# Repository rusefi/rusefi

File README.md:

*** test poke do not merge ***

<div align="center">

<b>GPL open-source ECU</b>

</div>

# rusEFI

[shop.rusEFI.com](https://www.shop.rusefi.com/)

# Download

Current binaries are always available on our [build server](http://rusefi.com/build_server/)

# Release Notes

See [the changelog](firmware/CHANGELOG.md)

# What do we have here?
 * [Firmware](/firmware) Source code for open source engine control unit for stm32 chips including [implementation overview](https://github.com/rusefi/rusefi/blob/master/firmware/readme.md)
 * [Hardware](/hardware) KiCAD files for our older PCBs
 * [rusEFI tuner](/java_console) rusEFI's own tuning software
 * [Simulator](/simulator) win32 or posix version of firmware allows to explore without any hardware
 * [Unit Tests](/unit_tests) Unit tests of firmware pieces [coverage report](https://rusefi.com/docs/unit_tests_coverage/)
 * [Misc tools](/java_tools) Misc development utilities
 * [Software Development process](misc/SoftwareDevelopmentProcess.md)

# External Links

 * [Forum](http://rusefi.com/forum)
 * [Documentation](https://wiki.rusefi.com)
 * [Doxygen documentation](http://rusefi.com/docs/html)
 * [General source code Q&A](http://rusefi.com/forum/viewtopic.php?f=5&t=10)
 * [Facebook](https://www.facebook.com/rusEfiECU)
 * [YouTube](https://www.youtube.com/user/rusefi)
 * [Patreon](https://www.patreon.com/rusefi)

# Cloning the repository
`git clone https://github.com/rusefi/rusefi.git`
Important note - we now use submodules:

`git submodule update --init`

# Building the Code

See [gcc_version_check.c](https://github.com/rusefi/rusefi/blob/master/firmware/gcc_version_check.c) for recommended version of GCC.

Check out https://rusefi.com/forum/viewtopic.php?f=5&t=9

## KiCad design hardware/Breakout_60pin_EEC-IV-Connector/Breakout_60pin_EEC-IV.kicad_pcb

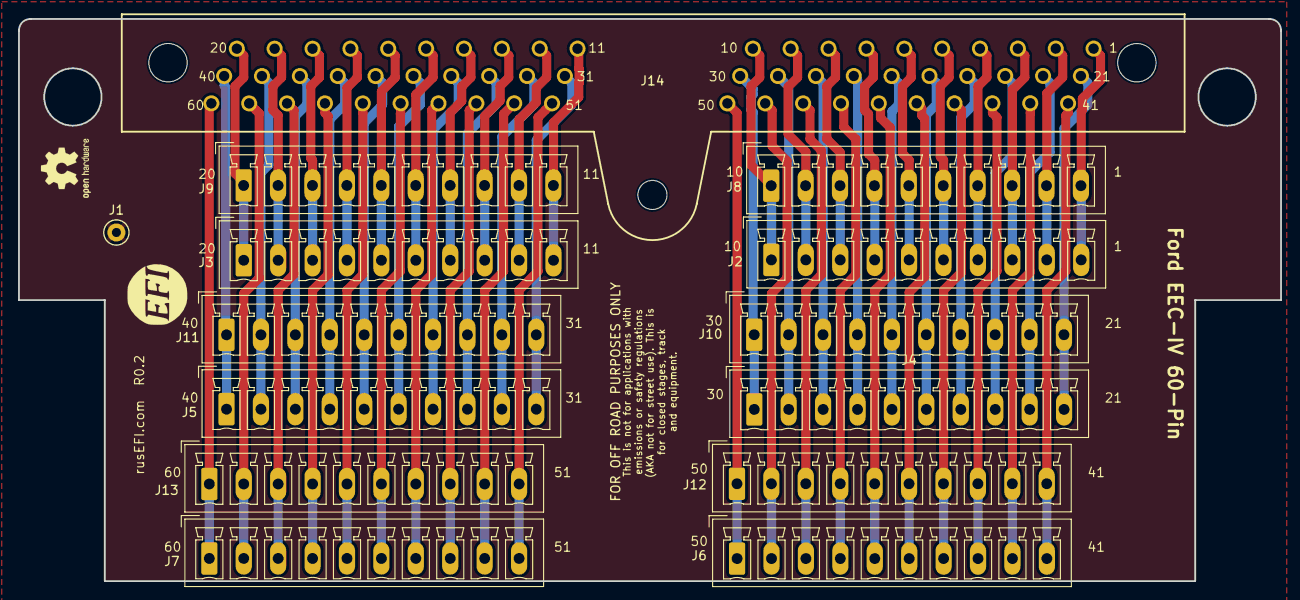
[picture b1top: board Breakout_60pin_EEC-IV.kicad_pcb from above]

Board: 2 copper layers, 139.7 x 62.2 mm, 17 parts (0 on the bottom side), 60 nets.

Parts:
G1: Disclaimer; Off_Road_Disclaimer
G2: LOGO
J1: Conn_01x01; TestPoint_Keystone_5000-5004_Miniature
J2, J3, J4, J5, J6, J7, J8, J9, J10, J11, J12, J13: Conn_01x10; PhoenixContact_MCV_1,5_10-G-3.81_1x10_P3.81mm_Vertical
J14: EEC-IV; eeciv
LOGO1: DNP; OSHW-Logo2_7.3x6mm_SilkScreen

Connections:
/1: J2.10, J8.10, J14.1
/5: J2.6, J8.6, J14.5
/10: J2.1, J8.1, J14.10
/11: J3.10, J9.10, J14.11
/15: J3.6, J9.6, J14.15
/25: J4.6, J10.6, J14.25
/30: J4.1, J10.1, J14.30
/31: J5.10, J11.10, J14.31
/35: J5.6, J11.6, J14.35
/40: J5.1, J11.1, J14.40
/41: J6.10, J12.10, J14.41
/45: J6.6, J12.6, J14.45
/50: J6.1, J12.1, J14.50
/53: J7.8, J13.8, J14.53
/54: J7.7, J13.7, J14.54
/55: J7.6, J13.6, J14.55
/60: J7.1, J13.1, J14.60
/420: J3.1, J9.1, J14.20
/421: J4.10, J10.10, J14.21
unnamed: J4.2, J10.2, J14.29
unnamed: J4.3, J10.3, J14.28
unnamed: J4.4, J10.4, J14.27
unnamed: J4.5, J10.5, J14.26
unnamed: J4.7, J10.7, J14.24
unnamed: J4.8, J10.8, J14.23
unnamed: J4.9, J10.9, J14.22
unnamed: J5.2, J11.2, J14.39
unnamed: J5.3, J11.3, J14.38
unnamed: J5.4, J11.4, J14.37
unnamed: J5.5, J11.5, J14.36
unnamed: J5.7, J11.7, J14.34
unnamed: J5.8, J11.8, J14.33
unnamed: J5.9, J11.9, J14.32
unnamed: J6.2, J12.2, J14.49
unnamed: J6.3, J12.3, J14.48
unnamed: J6.4, J12.4, J14.47
unnamed: J6.5, J12.5, J14.46
unnamed: J6.7, J12.7, J14.44
unnamed: J6.8, J12.8, J14.43
unnamed: J6.9, J12.9, J14.42
unnamed: J7.2, J13.2, J14.59
unnamed: J7.3, J13.3, J14.58
unnamed: J7.4, J13.4, J14.57
unnamed: J7.5, J13.5, J14.56
unnamed: J7.9, J13.9, J14.52
unnamed: J7.10, J13.10, J14.51
unnamed: J2.9, J8.9, J14.2
unnamed: J2.8, J8.8, J14.3
unnamed: J2.7, J8.7, J14.4
unnamed: J2.5, J8.5, J14.6
unnamed: J2.4, J8.4, J14.7
unnamed: J2.3, J8.3, J14.8
unnamed: J2.2, J8.2, J14.9
unnamed: J3.9, J9.9, J14.12
unnamed: J3.8, J9.8, J14.13
unnamed: J3.7, J9.7, J14.14
unnamed: J3.5, J9.5, J14.16
unnamed: J3.4, J9.4, J14.17
unnamed: J3.3, J9.3, J14.18
unnamed: J3.2, J9.2, J14.19

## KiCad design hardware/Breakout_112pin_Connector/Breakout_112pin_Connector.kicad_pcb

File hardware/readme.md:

# Connectors
Some vehicle-specific connector boards are also pretty nice if you want to keep original harness intact

See [Connectors wiki page](http://rusefi.com/wiki/index.php?title=Hardware:OEM_connectors)
todo: move Connectors wiki page content into git

* [35 pin](Breakout_35pin_MX7-C-35PL-C11-connector) Mazda TCU
* [38 pin](Breakout_38pin_NGC-connector) Chrysler NGC connector
* [48 pin](Breakout_48pin_174917-Connector) Mazda Miata NA6
* [52 pin](Breakout_52pin_172319-1-Connector) Mitsubishi Galant VR4
* [55 pin](Breakout_55pin_963063-15-Connector) TE Lada
* [55 pin](breakout_55pin-motronic-Connector) Motronic 1.5.x BMW/GM
* [60 pin](Breakout_60pin_EEC-IV-Connector) Ford EEC-IV
* [64 pin](Breakout_64pin_176122-6-Connector) Mazda Miata NA NB1, Honda Civic
* [68 pin](Breakout_68pin_966595-1_and_963356-1-Connector) Volkswagen Audi VAG
* [72 pin](Breakout_72pin_1123038-2-Connector) Mazda Miata NB2
* [88 pin](Breakout_88pin_VAG-Connector) Volkswagen Audi VAG
* [121 pin](Breakout_121pin_368255-2-Connector) Volkswagen Audi VAG
* [134 pin](Breakout_134pin_7-967288-1-Connector) BWM
* [154 pin](Breakout_154pin_284617-1-Connector) Volkswagen Audi VAG

# Modules
* [stm32 Brain board 48pin](mini48-stm32)
* [stm32 Brain board 100pin](brain_board)
* [stm32 Brain board 176pin](brain_board_176-pin)
* [CAN module](can_board) CAN using SN65HVD230
* [VR module](VR_Board) Variable Reluctance conditioner board VR MAX9926
* [Wideband module](CJ125_board) CJ125 Bosch Wideband board
* [VND5E025AKTR](PowerSSO-24_breakout) double channel high-side driver with analog current sense (used on Dodge Neon 2003 test mule)
* [BTS21400](DDPAK_breakout) ignition coil IGBT driver (used on Dodge Neon 2003 test mule)
* [TLE6240 module](low_side_tle6240) integrated low side switch (fabricated, not tested)
* [TLE6244 module](Breakout_TLE6244) integrated low side switch (never actually fabricated)
* [TLE8810ED module](https://github.com/rusefi/hw_modular/tree/master/TLE8110ED_breakout_board) integrated low side switch
* [MC33816](Common_Rail_MC33816) common rail driver - rusEFI has working GDI*
* [LM1949]([Low-Z_LM1949](https://github.com/rusefi/hw_legacy/tree/master/Low-Z_LM1949)) low impedance injector driver (never actually fabricated)

New modules are being added to https://github.com/rusefi/hw_modular

Some stuff we have given up on completely is located at https://github.com/rusefi/hw_legacy

Above mentioned modules are known to work unless stated otherwise

### More rusEFI hardware

See https://wiki.rusefi.com/Hardware

# Frankenso
Frankenso has moved to https://github.com/rusefi/rusefi-hardware/tree/main/classic-designs

# More info

 [Interactive Html Boms](https://rusefi.com/docs/ibom/)

See [Hardware status forum thread](http://rusefi.com/forum/viewtopic.php?f=4&t=260)
todo: move hardware status content into git

# Important note
rusEFI is currently transitioning from KiCAD 4 to KiCAD 5.

# Important note

Depends on libraries from https://github.com/rusefi/kicad-libraries

If you download complete repo do not forget to download libraries. If you git clone be sure to also

`git submodule update --init`

`git submodule update --init`

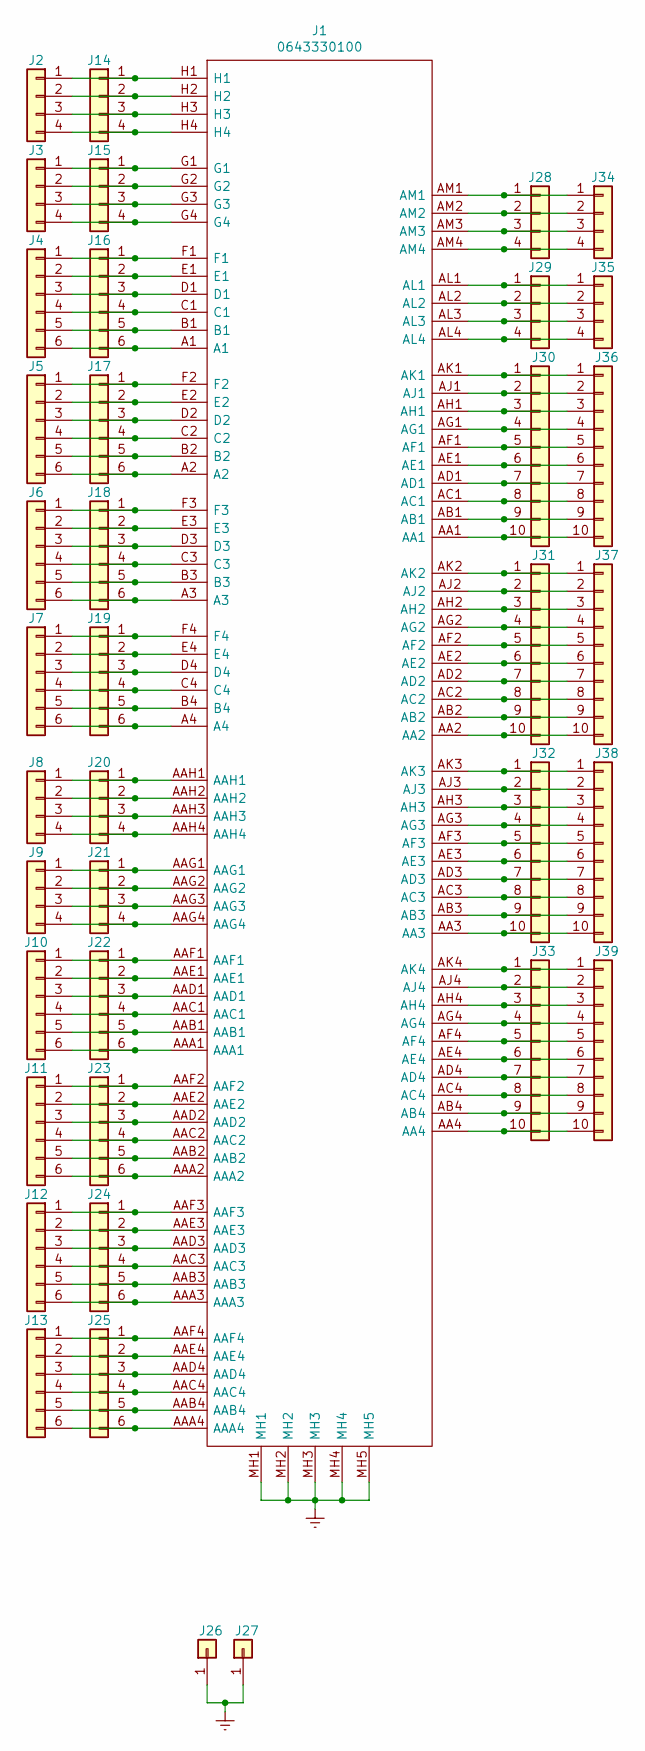
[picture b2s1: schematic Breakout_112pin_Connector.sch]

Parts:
J1: 0643330100; 64333-0100_1; Mouser Part Number N/A
J2, J3, J8, J9, J14, J15, J20, J21, J28, J29, J34, J35: Conn_01x04; Pin_Header_Straight_1x04_Pitch2.54mm
J4, J5, J6, J7, J10, J11, J12, J13, J16, J17, J18, J19, J22, J23, J24, J25: Conn_01x06; Pin_Header_Straight_1x06_Pitch2.54mm
J26, J27: Conn_01x01; Pin_Header_Straight_1x01_Pitch2.54mm
J30, J31, J32, J33, J36, J37, J38, J39: Conn_01x10; Pin_Header_Straight_1x10_Pitch2.54mm

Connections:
Earth: J1.MH1, J1.MH2, J1.MH3, J1.MH4, J1.MH5, J26.1, J27.1
unnamed: J1.A1, J4.6, J16.6
unnamed: J1.A2, J5.6, J17.6
unnamed: J1.A3, J6.6, J18.6
unnamed: J1.A4, J7.6, J19.6
unnamed: J1.AA1, J30.10, J36.10
unnamed: J1.AA2, J31.10, J37.10
unnamed: J1.AA3, J32.10, J38.10
unnamed: J1.AA4, J33.10, J39.10
unnamed: J1.AAA1, J10.6, J22.6
unnamed: J1.AAA2, J11.6, J23.6
unnamed: J1.AAA3, J12.6, J24.6
unnamed: J1.AAA4, J13.6, J25.6
unnamed: J1.AAB1, J10.5, J22.5
unnamed: J1.AAB2, J11.5, J23.5
unnamed: J1.AAB3, J12.5, J24.5
unnamed: J1.AAB4, J13.5, J25.5
unnamed: J1.AAC1, J10.4, J22.4
unnamed: J1.AAC2, J11.4, J23.4
unnamed: J1.AAC3, J12.4, J24.4
unnamed: J1.AAC4, J13.4, J25.4
unnamed: J1.AAD1, J10.3, J22.3
unnamed: J1.AAD2, J11.3, J23.3
unnamed: J1.AAD3, J12.3, J24.3
unnamed: J1.AAD4, J13.3, J25.3
unnamed: J1.AAE1, J10.2, J22.2
unnamed: J1.AAE2, J11.2, J23.2
unnamed: J1.AAE3, J12.2, J24.2
unnamed: J1.AAE4, J13.2, J25.2
unnamed: J1.AAF1, J10.1, J22.1
unnamed: J1.AAF2, J11.1, J23.1
unnamed: J1.AAF3, J12.1, J24.1
unnamed: J1.AAF4, J13.1, J25.1
unnamed: J1.AAG1, J9.1, J21.1
unnamed: J1.AAG2, J9.2, J21.2
unnamed: J1.AAG3, J9.3, J21.3
unnamed: J1.AAG4, J9.4, J21.4
unnamed: J1.AAH1, J8.1, J20.1
unnamed: J1.AAH2, J8.2, J20.2
unnamed: J1.AAH3, J8.3, J20.3
unnamed: J1.AAH4, J8.4, J20.4
unnamed: J1.AB1, J30.9, J36.9
unnamed: J1.AB2, J31.9, J37.9
unnamed: J1.AB3, J32.9, J38.9
unnamed: J1.AB4, J33.9, J39.9
unnamed: J1.AC1, J30.8, J36.8
unnamed: J1.AC2, J31.8, J37.8
unnamed: J1.AC3, J32.8, J38.8
unnamed: J1.AC4, J33.8, J39.8
unnamed: J1.AD1, J30.7, J36.7
unnamed: J1.AD2, J31.7, J37.7
unnamed: J1.AD3, J32.7, J38.7
unnamed: J1.AD4, J33.7, J39.7
unnamed: J1.AE1, J30.6, J36.6
unnamed: J1.AE2, J31.6, J37.6
unnamed: J1.AE3, J32.6, J38.6
unnamed: J1.AE4, J33.6, J39.6
unnamed: J1.AF1, J30.5, J36.5
unnamed: J1.AF2, J31.5, J37.5
unnamed: J1.AF3, J32.5, J38.5
unnamed: J1.AF4, J33.5, J39.5
unnamed: J1.AG1, J30.4, J36.4
unnamed: J1.AG2, J31.4, J37.4
unnamed: J1.AG3, J32.4, J38.4
unnamed: J1.AG4, J33.4, J39.4
unnamed: J1.AH1, J30.3, J36.3
unnamed: J1.AH2, J31.3, J37.3
unnamed: J1.AH3, J32.3, J38.3
unnamed: J1.AH4, J33.3, J39.3
unnamed: J1.AJ1, J30.2, J36.2
unnamed: J1.AJ2, J31.2, J37.2
unnamed: J1.AJ3, J32.2, J38.2
unnamed: J1.AJ4, J33.2, J39.2
unnamed: J1.AK1, J30.1, J36.1
unnamed: J1.AK2, J31.1, J37.1
unnamed: J1.AK3, J32.1, J38.1
unnamed: J1.AK4, J33.1, J39.1
unnamed: J1.AL1, J29.1, J35.1
unnamed: J1.AL2, J29.2, J35.2
unnamed: J1.AL3, J29.3, J35.3
unnamed: J1.AL4, J29.4, J35.4
unnamed: J1.AM1, J28.1, J34.1
unnamed: J1.AM2, J28.2, J34.2
unnamed: J1.AM3, J28.3, J34.3
unnamed: J1.AM4, J28.4, J34.4
unnamed: J1.B1, J4.5, J16.5
unnamed: J1.B2, J5.5, J17.5
unnamed: J1.B3, J6.5, J18.5
unnamed: J1.B4, J7.5, J19.5
unnamed: J1.C1, J4.4, J16.4
unnamed: J1.C2, J5.4, J17.4
unnamed: J1.C3, J6.4, J18.4
unnamed: J1.C4, J7.4, J19.4
unnamed: J1.D1, J4.3, J16.3
unnamed: J1.D2, J5.3, J17.3
unnamed: J1.D3, J6.3, J18.3
unnamed: J1.D4, J7.3, J19.3
unnamed: J1.E1, J4.2, J16.2
unnamed: J1.E2, J5.2, J17.2
unnamed: J1.E3, J6.2, J18.2
unnamed: J1.E4, J7.2, J19.2
unnamed: J1.F1, J4.1, J16.1
unnamed: J1.F2, J5.1, J17.1
unnamed: J1.F3, J6.1, J18.1
unnamed: J1.F4, J7.1, J19.1
unnamed: J1.G1, J3.1, J15.1
unnamed: J1.G2, J3.2, J15.2
unnamed: J1.G3, J3.3, J15.3
unnamed: J1.G4, J3.4, J15.4
unnamed: J1.H1, J2.1, J14.1
unnamed: J1.H2, J2.2, J14.2
unnamed: J1.H3, J2.3, J14.3
unnamed: J1.H4, J2.4, J14.4

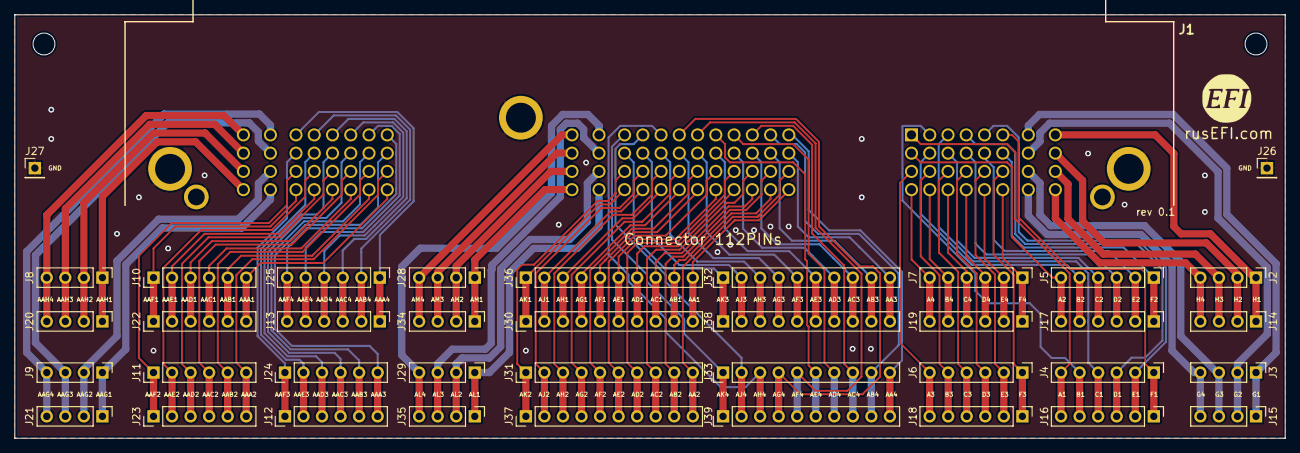
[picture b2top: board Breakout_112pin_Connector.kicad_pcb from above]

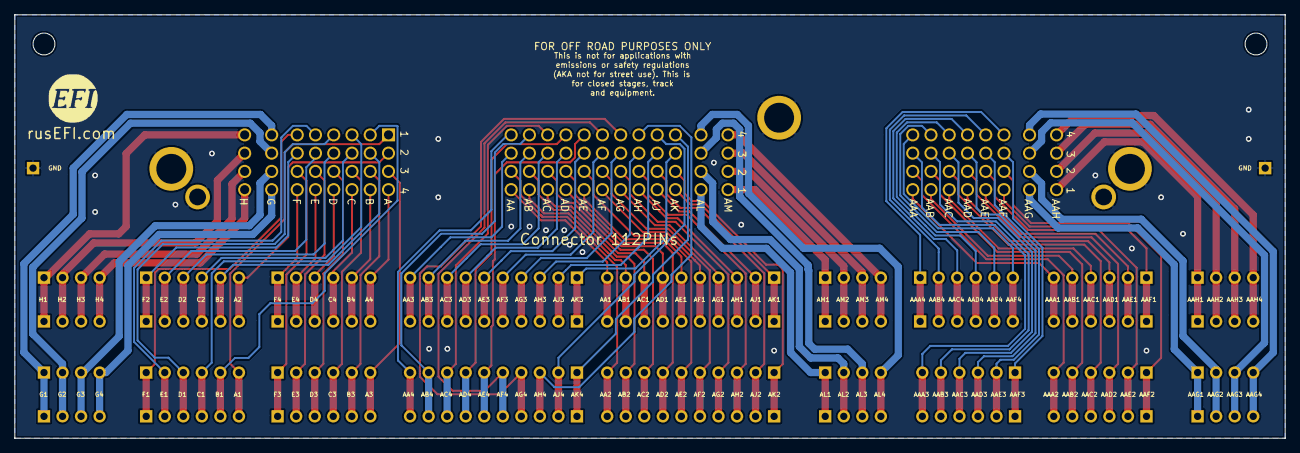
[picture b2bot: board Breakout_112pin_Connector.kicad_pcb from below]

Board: 2 copper layers, 174.0 x 58.0 mm, 42 parts (2 on the bottom side), 113 nets.

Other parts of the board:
G?: LOGO
G?#2: LOGO
G?#3: Disclaimer; Off_Road_Disclaimer

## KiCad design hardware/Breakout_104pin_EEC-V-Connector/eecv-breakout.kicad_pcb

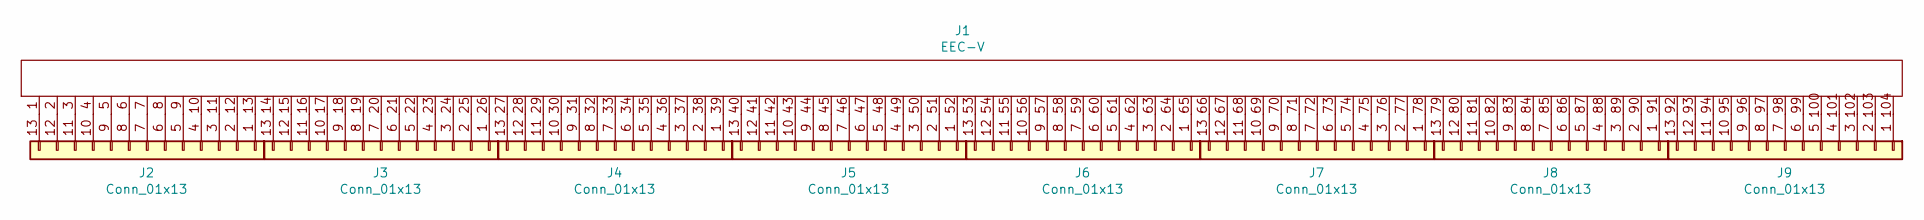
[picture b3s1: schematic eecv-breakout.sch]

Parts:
J1: EEC-V; eecv
J2, J3, J4, J5, J6, J7, J8, J9: Conn_01x13; PhoenixContact_MCV_1,5_13-G-3.81_1x13_P3.81mm_Vertical

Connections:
unnamed: J1.1, J2.13
unnamed: J1.2, J2.12
unnamed: J1.3, J2.11
unnamed: J1.4, J2.10
unnamed: J1.5, J2.9
unnamed: J1.6, J2.8
unnamed: J1.7, J2.7
unnamed: J1.8, J2.6
unnamed: J1.9, J2.5
unnamed: J1.10, J2.4
unnamed: J1.11, J2.3
unnamed: J1.12, J2.2
unnamed: J1.13, J2.1
unnamed: J1.14, J3.13
unnamed: J1.15, J3.12
unnamed: J1.16, J3.11
unnamed: J1.17, J3.10
unnamed: J1.18, J3.9
unnamed: J1.19, J3.8
unnamed: J1.20, J3.7
unnamed: J1.21, J3.6
unnamed: J1.22, J3.5
unnamed: J1.23, J3.4
unnamed: J1.24, J3.3
unnamed: J1.25, J3.2
unnamed: J1.26, J3.1
unnamed: J1.27, J4.13
unnamed: J1.28, J4.12
unnamed: J1.29, J4.11
unnamed: J1.30, J4.10
unnamed: J1.31, J4.9
unnamed: J1.32, J4.8
unnamed: J1.33, J4.7
unnamed: J1.34, J4.6
unnamed: J1.35, J4.5
unnamed: J1.36, J4.4
unnamed: J1.37, J4.3
unnamed: J1.38, J4.2
unnamed: J1.39, J4.1
unnamed: J1.40, J5.13
unnamed: J1.41, J5.12
unnamed: J1.42, J5.11
unnamed: J1.43, J5.10
unnamed: J1.44, J5.9
unnamed: J1.45, J5.8
unnamed: J1.46, J5.7
unnamed: J1.47, J5.6
unnamed: J1.48, J5.5
unnamed: J1.49, J5.4
unnamed: J1.50, J5.3
unnamed: J1.51, J5.2
unnamed: J1.52, J5.1
unnamed: J1.53, J6.13
unnamed: J1.54, J6.12
unnamed: J1.55, J6.11
unnamed: J1.56, J6.10
unnamed: J1.57, J6.9
unnamed: J1.58, J6.8
unnamed: J1.59, J6.7
unnamed: J1.60, J6.6
unnamed: J1.61, J6.5
unnamed: J1.62, J6.4
unnamed: J1.63, J6.3
unnamed: J1.64, J6.2
unnamed: J1.65, J6.1
unnamed: J1.66, J7.13
unnamed: J1.67, J7.12
unnamed: J1.68, J7.11
unnamed: J1.69, J7.10
unnamed: J1.70, J7.9
unnamed: J1.71, J7.8
unnamed: J1.72, J7.7
unnamed: J1.73, J7.6
unnamed: J1.74, J7.5
unnamed: J1.75, J7.4
unnamed: J1.76, J7.3
unnamed: J1.77, J7.2
unnamed: J1.78, J7.1
unnamed: J1.79, J8.13
unnamed: J1.80, J8.12
unnamed: J1.81, J8.11
unnamed: J1.82, J8.10
unnamed: J1.83, J8.9
unnamed: J1.84, J8.8
unnamed: J1.85, J8.7
unnamed: J1.86, J8.6
unnamed: J1.87, J8.5
unnamed: J1.88, J8.4
unnamed: J1.89, J8.3
unnamed: J1.90, J8.2
unnamed: J1.91, J8.1
unnamed: J1.92, J9.13
unnamed: J1.93, J9.12
unnamed: J1.94, J9.11
unnamed: J1.95, J9.10
unnamed: J1.96, J9.9
unnamed: J1.97, J9.8
unnamed: J1.98, J9.7
unnamed: J1.99, J9.6
unnamed: J1.100, J9.5
unnamed: J1.101, J9.4
unnamed: J1.102, J9.3
unnamed: J1.103, J9.2
unnamed: J1.104, J9.1

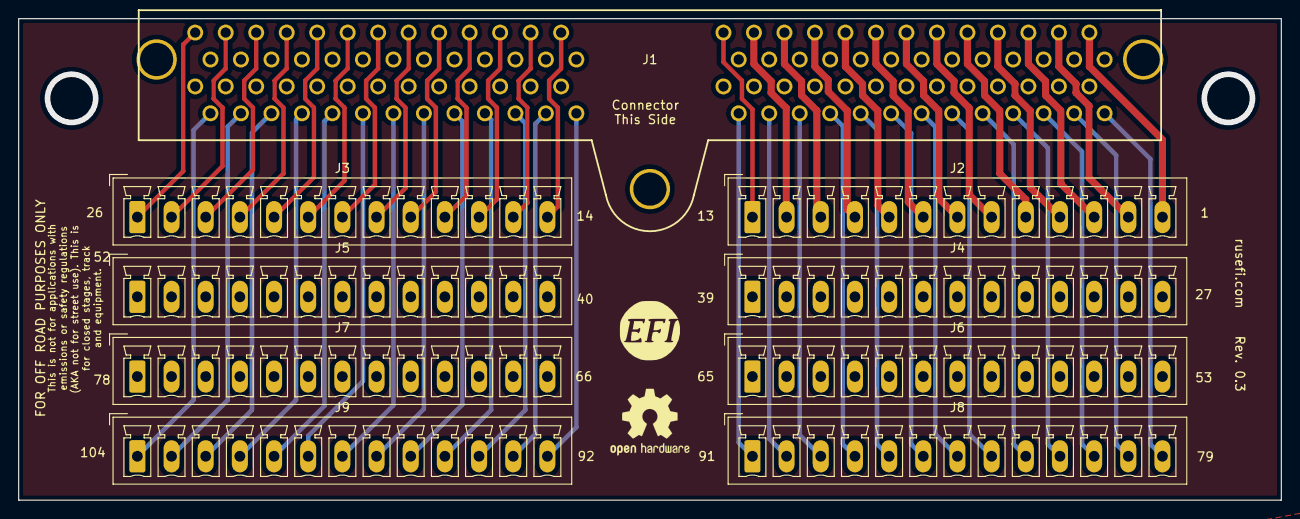
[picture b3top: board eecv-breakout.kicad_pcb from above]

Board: 4 copper layers, 140.8 x 53.7 mm, 11 parts (0 on the bottom side), 104 nets.

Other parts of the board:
G?: LOGO
G?#2: Disclaimer; Off_Road_Disclaimer

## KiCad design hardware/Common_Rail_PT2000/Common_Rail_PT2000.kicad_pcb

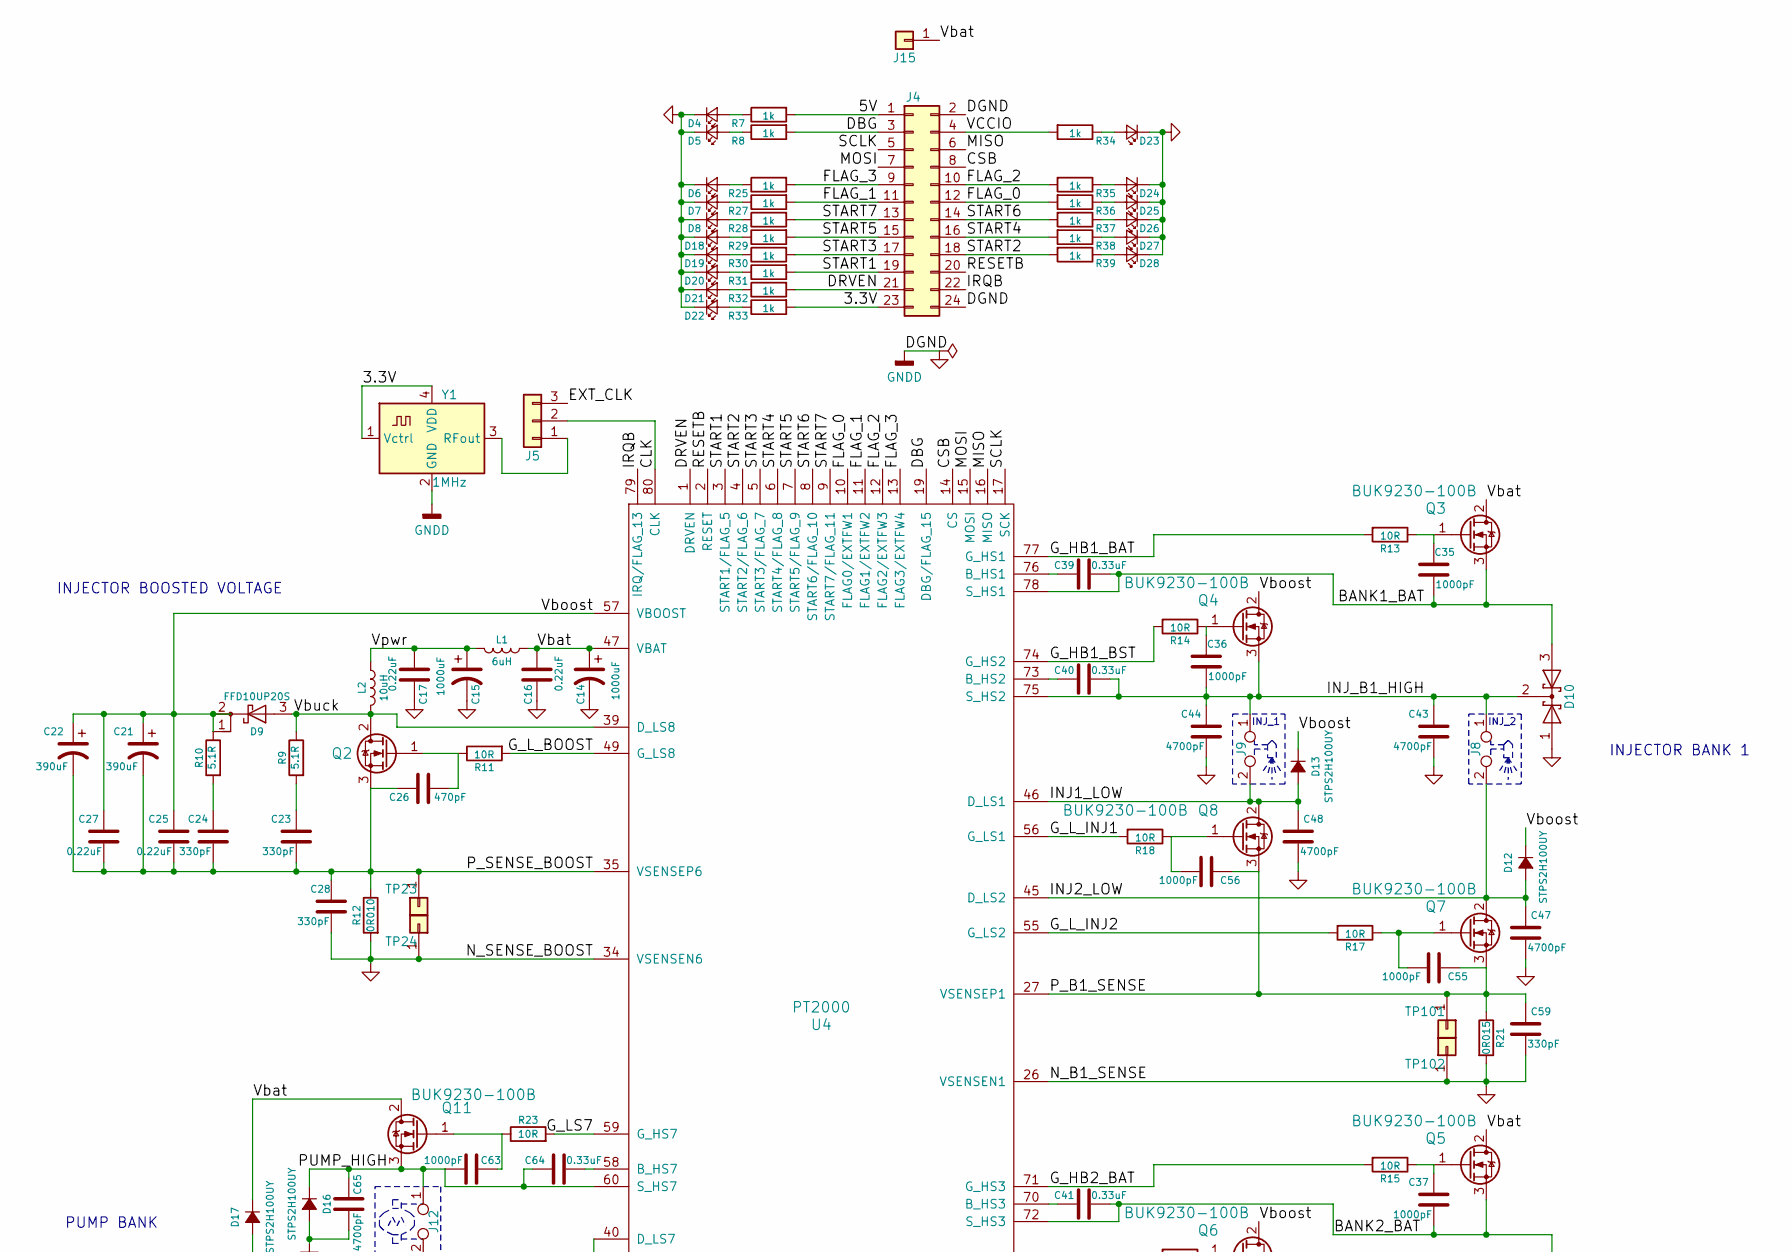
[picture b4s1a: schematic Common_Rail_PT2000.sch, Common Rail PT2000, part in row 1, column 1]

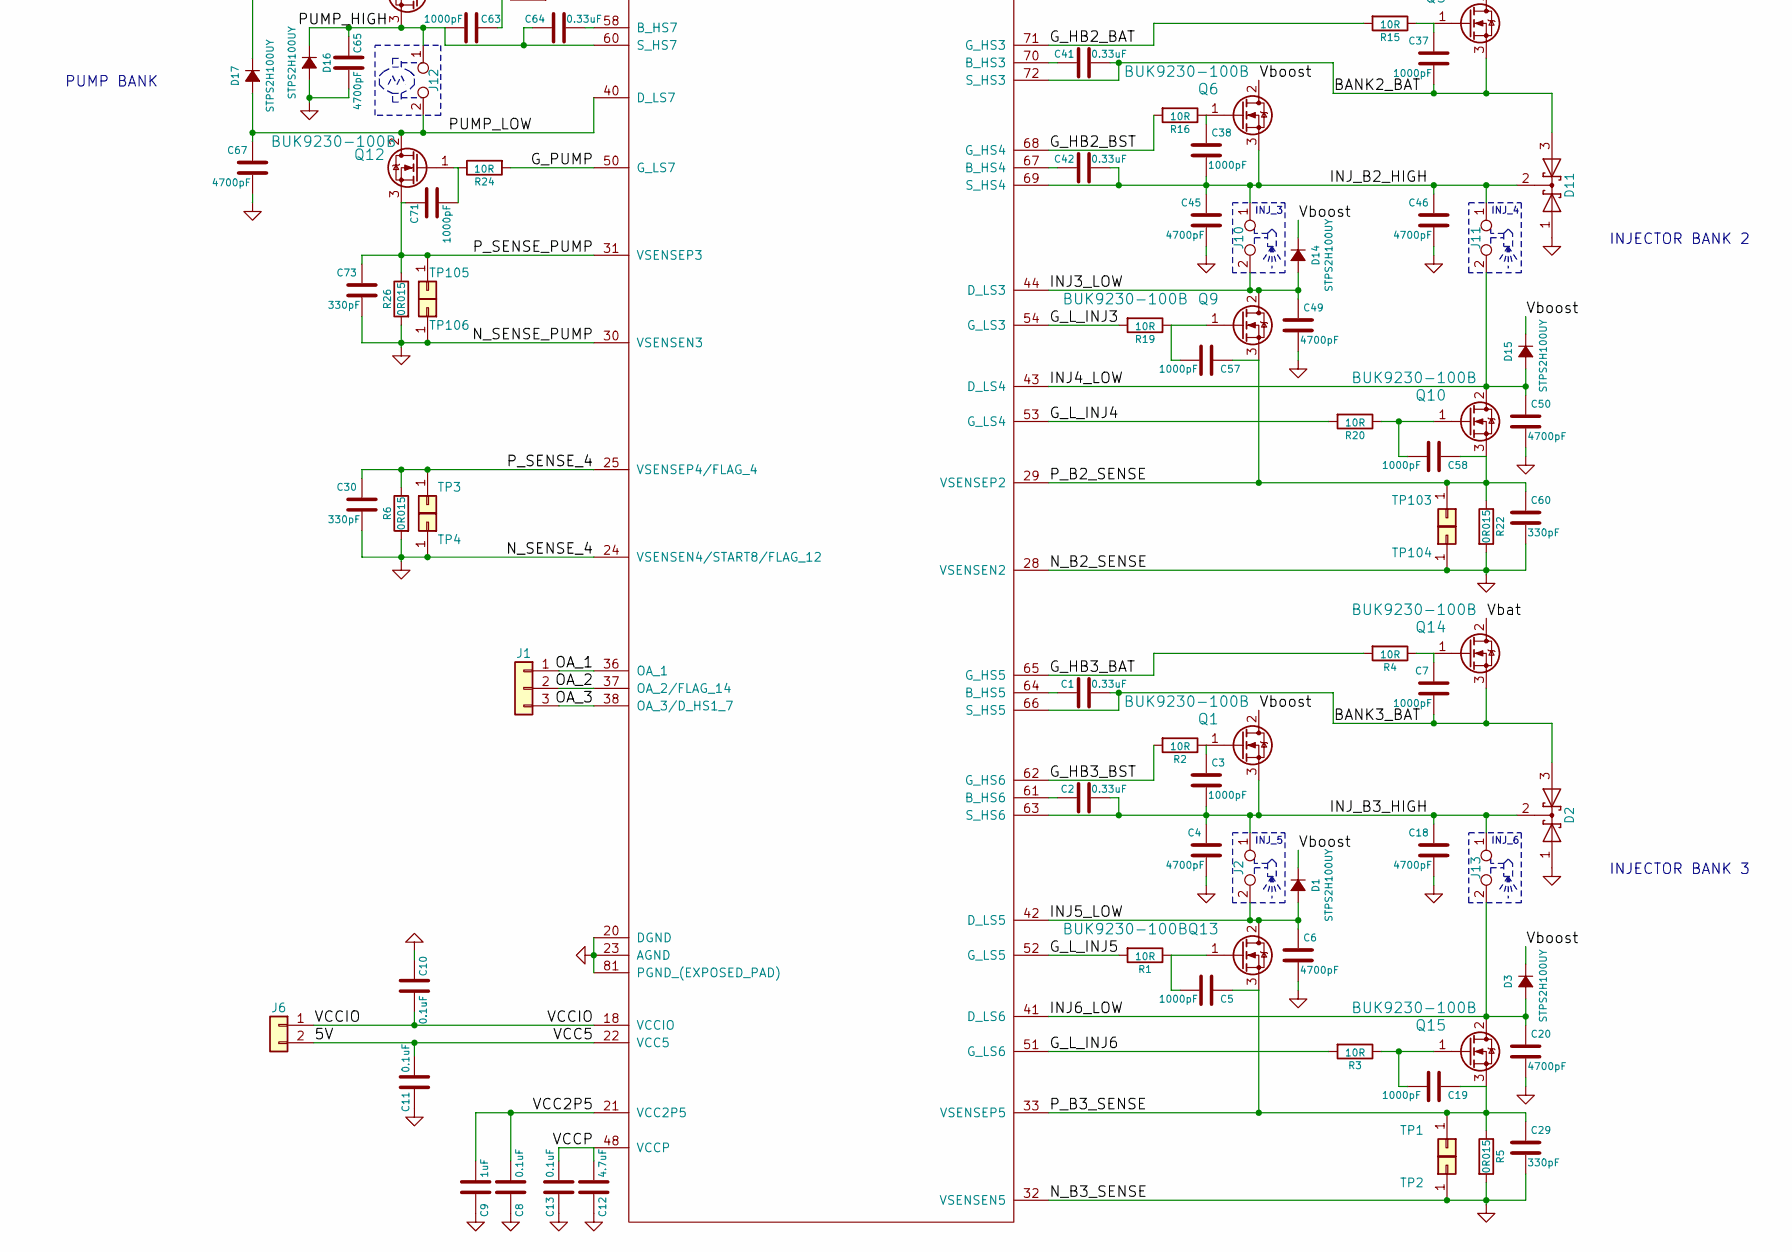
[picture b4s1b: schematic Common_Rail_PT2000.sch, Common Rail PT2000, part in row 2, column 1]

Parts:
C1, C2, C39, C40, C41, C42, C64: 0.33uF; C_0805
C3, C5, C7, C19, C35, C36, C37, C38, C55, C56, C57, C58, C63, C71: 1000pF; C_0805
C4, C6, C18, C20, C43, C44, C45, C46, C47, C48, C49, C50, C65, C67: 4700pF; C_0805
C8, C10, C11, C13: 0.1uF; C_0805
C9: 1uF; C_0805
C12: 4.7uF; C_0805
C14, C15: 1000uF; CP_Radial_D22.0mm_P10.00mm_SnapIn
C16, C17, C25, C27: 0.22uF; C_0805
C21, C22: 390uF; CP_Radial_D16.0mm_P7.50mm
C23, C24, C28, C29, C30, C59, C60, C73: 330pF; C_0805
C26: 470pF; C_0805
D1, D3, D12, D13, D14, D15, D16, D17: STPS2H100UY; D_SMB
D2, D10, D11: SBR10200CTL; TO-252-2Lead
D4, D5, D6, D7, D8, D18, D19, D20, D21, D22, D23, D24, D25, D26, D27, D28: LED_Small; LED_0805
D9: FFD10UP20S; TO-252-2Lead
J1, J5: CONN_01X03; Pin_Header_Straight_1x03_Pitch2.54mm
J2, J8, J9, J10, J11, J12, J13: INJ_Term; TerminalBlock_bornier-2_P5.08mm
J4: CONN_02X08; Pin_Header_Straight_2x12_Pitch2.54mm
J6: CONN_01X03; Pin_Header_Straight_1x02_Pitch1.27mm
J15: Conn_01x01; Pin_Header_Straight_1x01_Pitch2.54mm
L1: 6uH; 744710610-Inductor
L2: 10uH; IHLP6767GZER100M01
Q1, Q2, Q3, Q4, Q5, Q6, Q7, Q8, Q9, Q10, Q11, Q12, Q13, Q14, Q15: BUK9230-100B; TO-252-2Lead
R1, R2, R3, R4, R11, R13, R14, R15, R16, R17, R18, R19, R20, R23, R24: 10R; R_0805
R5, R6, R21, R22, R26: 0R015; R_1206_HandSoldering
R7, R8, R25, R27, R28, R29, R30, R31, R32, R33, R34, R35, R36, R37, R38, R39: 1k; R_0805
R9, R10: 5.1R; R_0805
R12: 0R010; R_1206_HandSoldering
TP1, TP2, TP3, TP4, TP23, TP24, TP101, TP102, TP103, TP104, TP105, TP106: Conn_01x01; PINTST
U4: PT2000; LQFP-80_12x12mm_Pitch0.5mmThermal
Y1: 1MHz; Crystal_SMD_SeikoEpson_MC306-4pin_8.0x3.2mm

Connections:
/3.3V: J4.23, R33.2, Y1.1 (Vctrl), Y1.4 (VDD)
/5V: C11.1, J4.1, J6.2, R7.2, U4.22 (VCC5)
/BANK1_BAT: C35.2, C39.2, D10.3 (A), Q3.3 (S), U4.78 (S_HS1)
/BANK2_BAT: C37.2, C41.2, D11.3 (A), Q5.3 (S), U4.72 (S_HS3)
/BANK3_BAT: C1.2, C7.2, D2.3 (A), Q14.3 (S), U4.66 (S_HS5)
/CLK: J5.2, U4.80 (CLK)
/CSB: J4.8, U4.14 (CS)
/DBG: J4.3, R8.2, U4.19 (DBG/FLAG_15)
/DRVEN: J4.21, R32.2, U4.1 (DRVEN)
/FLAG_0: J4.12, R36.2, U4.10 (FLAG0/EXTFW1)
/FLAG_1: J4.11, R27.2, U4.11 (FLAG1/EXTFW2)
/FLAG_2: J4.10, R35.2, U4.12 (FLAG2/EXTFW3)
/FLAG_3: J4.9, R25.2, U4.13 (FLAG3/EXTFW4)
/G_HB1_BAT: R13.2, U4.77 (G_HS1)
/G_HB1_BST: R14.2, U4.74 (G_HS2)
/G_HB2_BAT: R15.2, U4.71 (G_HS3)
/G_HB2_BST: R16.2, U4.68 (G_HS4)
/G_HB3_BAT: R4.2, U4.65 (G_HS5)
/G_HB3_BST: R2.2, U4.62 (G_HS6)
/G_LS7: R23.2, U4.59 (G_HS7)
/G_L_BOOST: R11.2, U4.49 (G_LS8)
/G_L_INJ1: R18.2, U4.56 (G_LS1)
/G_L_INJ2: R17.2, U4.55 (G_LS2)
/G_L_INJ3: R19.2, U4.54 (G_LS3)
/G_L_INJ4: R20.2, U4.53 (G_LS4)
/G_L_INJ5: R1.2, U4.52 (G_LS5)
/G_L_INJ6: R3.2, U4.51 (G_LS6)
/G_PUMP: R24.2, U4.50 (G_LS7)
/INJ1_LOW: C48.1, D13.2 (A), J9.2, Q8.2 (D), U4.46 (D_LS1)
/INJ2_LOW: C47.1, D12.2 (A), J8.2, Q7.2 (D), U4.45 (D_LS2)
/INJ3_LOW: C49.1, D14.2 (A), J10.2, Q9.2 (D), U4.44 (D_LS3)
/INJ4_LOW: C50.1, D15.2 (A), J11.2, Q10.2 (D), U4.43 (D_LS4)
/INJ5_LOW: C6.1, D1.2 (A), J2.2, Q13.2 (D), U4.42 (D_LS5)
/INJ6_LOW: C20.1, D3.2 (A), J13.2, Q15.2 (D), U4.41 (D_LS6)
/INJ_B1_HIGH: C36.2, C40.2, C43.1, C44.1, D10.2 (K), J8.1, J9.1, Q4.3 (S), U4.75 (S_HS2)
/INJ_B2_HIGH: C38.2, C42.2, C45.1, C46.1, D11.2 (K), J10.1, J11.1, Q6.3 (S), U4.69 (S_HS4)
/INJ_B3_HIGH: C2.2, C3.2, C4.1, C18.1, D2.2 (K), J2.1, J13.1, Q1.3 (S), U4.63 (S_HS6)
/IRQB: J4.22, U4.79 (IRQ/FLAG_13)
/MISO: J4.6, U4.16 (MISO)
/MOSI: J4.7, U4.15 (MOSI)
/OA_1: J1.1, U4.36 (OA_1)
/OA_2: J1.2, U4.37 (OA_2/FLAG_14)
/OA_3: J1.3, U4.38 (OA_3/D_HS1_7)
/PUMP_HIGH: C63.2, C64.1, C65.1, D16.1 (K), J12.1, Q11.3 (S), U4.60 (S_HS7)
/PUMP_LOW: C67.1, D17.2 (A), J12.2, Q12.2 (D), U4.40 (D_LS7)
/P_B1_SENSE: C55.1, C56.1, C59.1, Q7.3 (S), Q8.3 (S), R21.1, TP101.1, U4.27 (VSENSEP1)
/P_B2_SENSE: C57.1, C58.1, C60.1, Q9.3 (S), Q10.3 (S), R22.1, TP103.1, U4.29 (VSENSEP2)
/P_B3_SENSE: C5.1, C19.1, C29.1, Q13.3 (S), Q15.3 (S), R5.1, TP1.1, U4.33 (VSENSEP5)
/P_SENSE_4: C30.1, R6.1, TP3.1, U4.25 (VSENSEP4/FLAG_4)
/P_SENSE_BOOST: C21.2, C22.2, C23.2, C24.2, C25.2, C26.1, C27.2, C28.1, Q2.3 (S), R12.1, TP23.1, U4.35 (VSENSEP6)
/P_SENSE_PUMP: C71.1, C73.1, Q12.3 (S), R26.1, TP105.1, U4.31 (VSENSEP3)
/RESETB: J4.20, U4.2 (RESET)
/SCLK: J4.5, U4.17 (SCK)
/START1: J4.19, R31.2, U4.3 (START1/FLAG_5)
/START2: J4.18, R39.2, U4.4 (START2/FLAG_6)
/START3: J4.17, R30.2, U4.5 (START3/FLAG_7)
/START4: J4.16, R38.2, U4.6 (START4/FLAG_8)
/START5: J4.15, R29.2, U4.7 (START5/FLAG_9)
/START6: J4.14, R37.2, U4.8 (START6/FLAG_10)
/START7: J4.13, R28.2, U4.9 (START7/FLAG_11)
/VCC2P5: C8.1, C9.1, U4.21 (VCC2P5)
/VCCIO: C10.1, J4.4, J6.1, R34.2, U4.18 (VCCIO)
/VCCP: C12.1, C13.1, U4.48 (VCCP)
/Vbat: C14.1, C16.1, D17.1 (K), J15.1, L1.2, Q3.2 (D), Q5.2 (D), Q11.2 (D), Q14.2 (D), U4.47 (VBAT)
/Vboost: C21.1, C22.1, C25.1, C27.1, D1.1 (K), D3.1 (K), D9.1 (K), D9.2 (K), D12.1 (K), D13.1 (K), D14.1 (K), D15.1 (K), Q1.2 (D), Q4.2 (D), Q6.2 (D), R10.1, U4.57 (VBOOST)
/Vbuck: D9.3 (A), L2.1, Q2.2 (D), R9.1, U4.39 (D_LS8)
/Vpwr: C15.1, C17.1, L1.1, L2.2
GND: C4.2, C6.2, C8.2, C9.2, C10.2, C11.2, C12.2, C13.2, C14.2, C15.2, C16.2, C17.2, C18.2, C20.2, C28.2, C29.2, C30.2, C43.2, C44.2, C45.2, C46.2, C47.2, C48.2, C49.2, C50.2, C59.2, C60.2, C65.2, C67.2, C73.2, D2.1 (A), D4.1 (K), D5.1 (K), D6.1 (K), D7.1 (K), D8.1 (K), D10.1 (A), D11.1 (A), D16.2 (A), D18.1 (K), D19.1 (K), D20.1 (K), D21.1 (K), D22.1 (K), D23.1 (K), D24.1 (K), D25.1 (K), D26.1 (K), D27.1 (K), D28.1 (K), J4.2, J4.24, R5.2, R6.2, R12.2, R21.2, R22.2, R26.2, TP2.1, TP4.1, TP24.1, TP102.1, TP104.1, TP106.1, U4.20 (DGND), U4.23 (AGND), U4.24 (VSENSEN4/START8/FLAG_12), U4.26 (VSENSEN1), U4.28 (VSENSEN2), U4.30 (VSENSEN3), U4.32 (VSENSEN5), U4.34 (VSENSEN6), U4.81 (PGND_(EXPOSED_PAD)), Y1.2 (GND)
unnamed: C1.1, U4.64 (B_HS5)
unnamed: C2.1, U4.61 (B_HS6)
unnamed: C3.1, Q1.1 (G), R2.1
unnamed: C5.2, Q13.1 (G), R1.1
unnamed: C7.1, Q14.1 (G), R4.1
unnamed: C19.2, Q15.1 (G), R3.1
unnamed: C23.1, R9.2
unnamed: C24.1, R10.2
unnamed: C26.2, Q2.1 (G), R11.1
unnamed: C35.1, Q3.1 (G), R13.1
unnamed: C36.1, Q4.1 (G), R14.1
unnamed: C37.1, Q5.1 (G), R15.1
unnamed: C38.1, Q6.1 (G), R16.1
unnamed: C39.1, U4.76 (B_HS1)
unnamed: C40.1, U4.73 (B_HS2)
unnamed: C41.1, U4.70 (B_HS3)
unnamed: C42.1, U4.67 (B_HS4)
unnamed: C55.2, Q7.1 (G), R17.1
unnamed: C56.2, Q8.1 (G), R18.1
unnamed: C57.2, Q9.1 (G), R19.1
unnamed: C58.2, Q10.1 (G), R20.1
unnamed: C63.1, Q11.1 (G), R23.1
unnamed: C64.2, U4.58 (B_HS7)
unnamed: C71.2, Q12.1 (G), R24.1
unnamed: D4.2 (A), R7.1
unnamed: D5.2 (A), R8.1
unnamed: D6.2 (A), R25.1
unnamed: D7.2 (A), R27.1
unnamed: D8.2 (A), R28.1
unnamed: D18.2 (A), R29.1
unnamed: D19.2 (A), R30.1
unnamed: D20.2 (A), R31.1
unnamed: D21.2 (A), R32.1
unnamed: D22.2 (A), R33.1
unnamed: D23.2 (A), R34.1
unnamed: D24.2 (A), R35.1
unnamed: D25.2 (A), R36.1
unnamed: D26.2 (A), R37.1
unnamed: D27.2 (A), R38.1
unnamed: D28.2 (A), R39.1
unnamed: J5.1, Y1.3 (RFout)

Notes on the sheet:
PUMP BANK
INJECTOR BOOSTED VOLTAGE
INJECTOR BANK 2
INJECTOR BANK 1
INJ_2
INJ_1
INJ_3
INJ_4
INJECTOR BANK 3
INJ_5
INJ_6

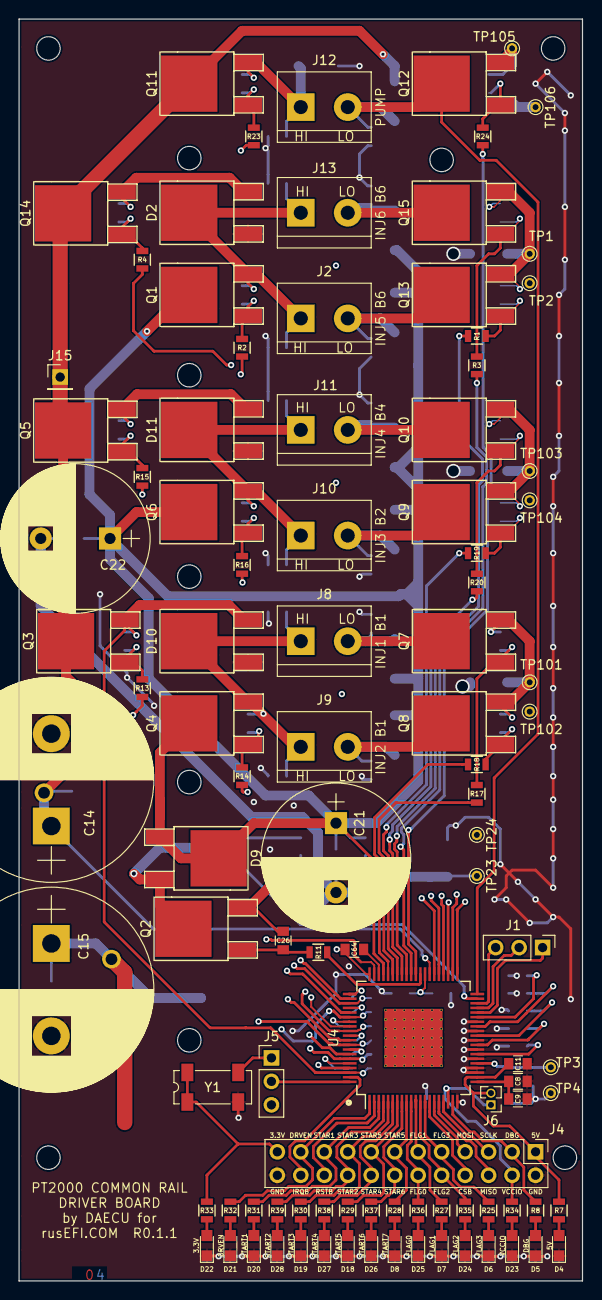
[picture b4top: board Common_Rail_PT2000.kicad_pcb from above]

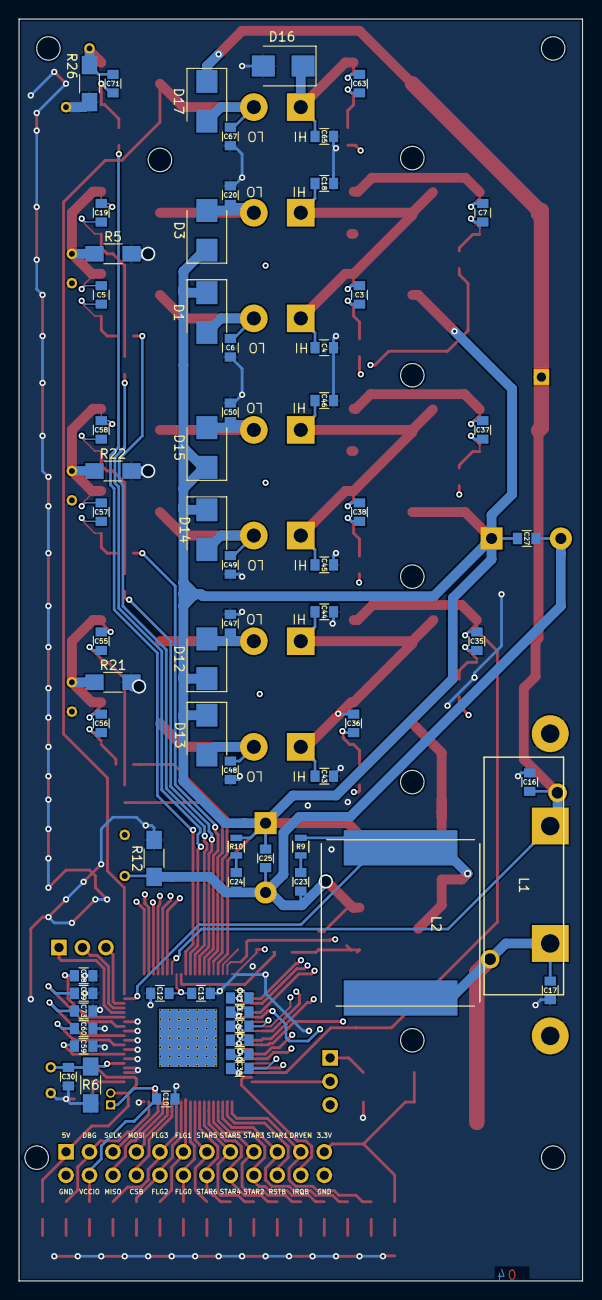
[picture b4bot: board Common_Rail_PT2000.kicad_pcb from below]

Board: 4 copper layers, 61.0 x 136.5 mm, 168 parts (67 on the bottom side), 109 nets.
